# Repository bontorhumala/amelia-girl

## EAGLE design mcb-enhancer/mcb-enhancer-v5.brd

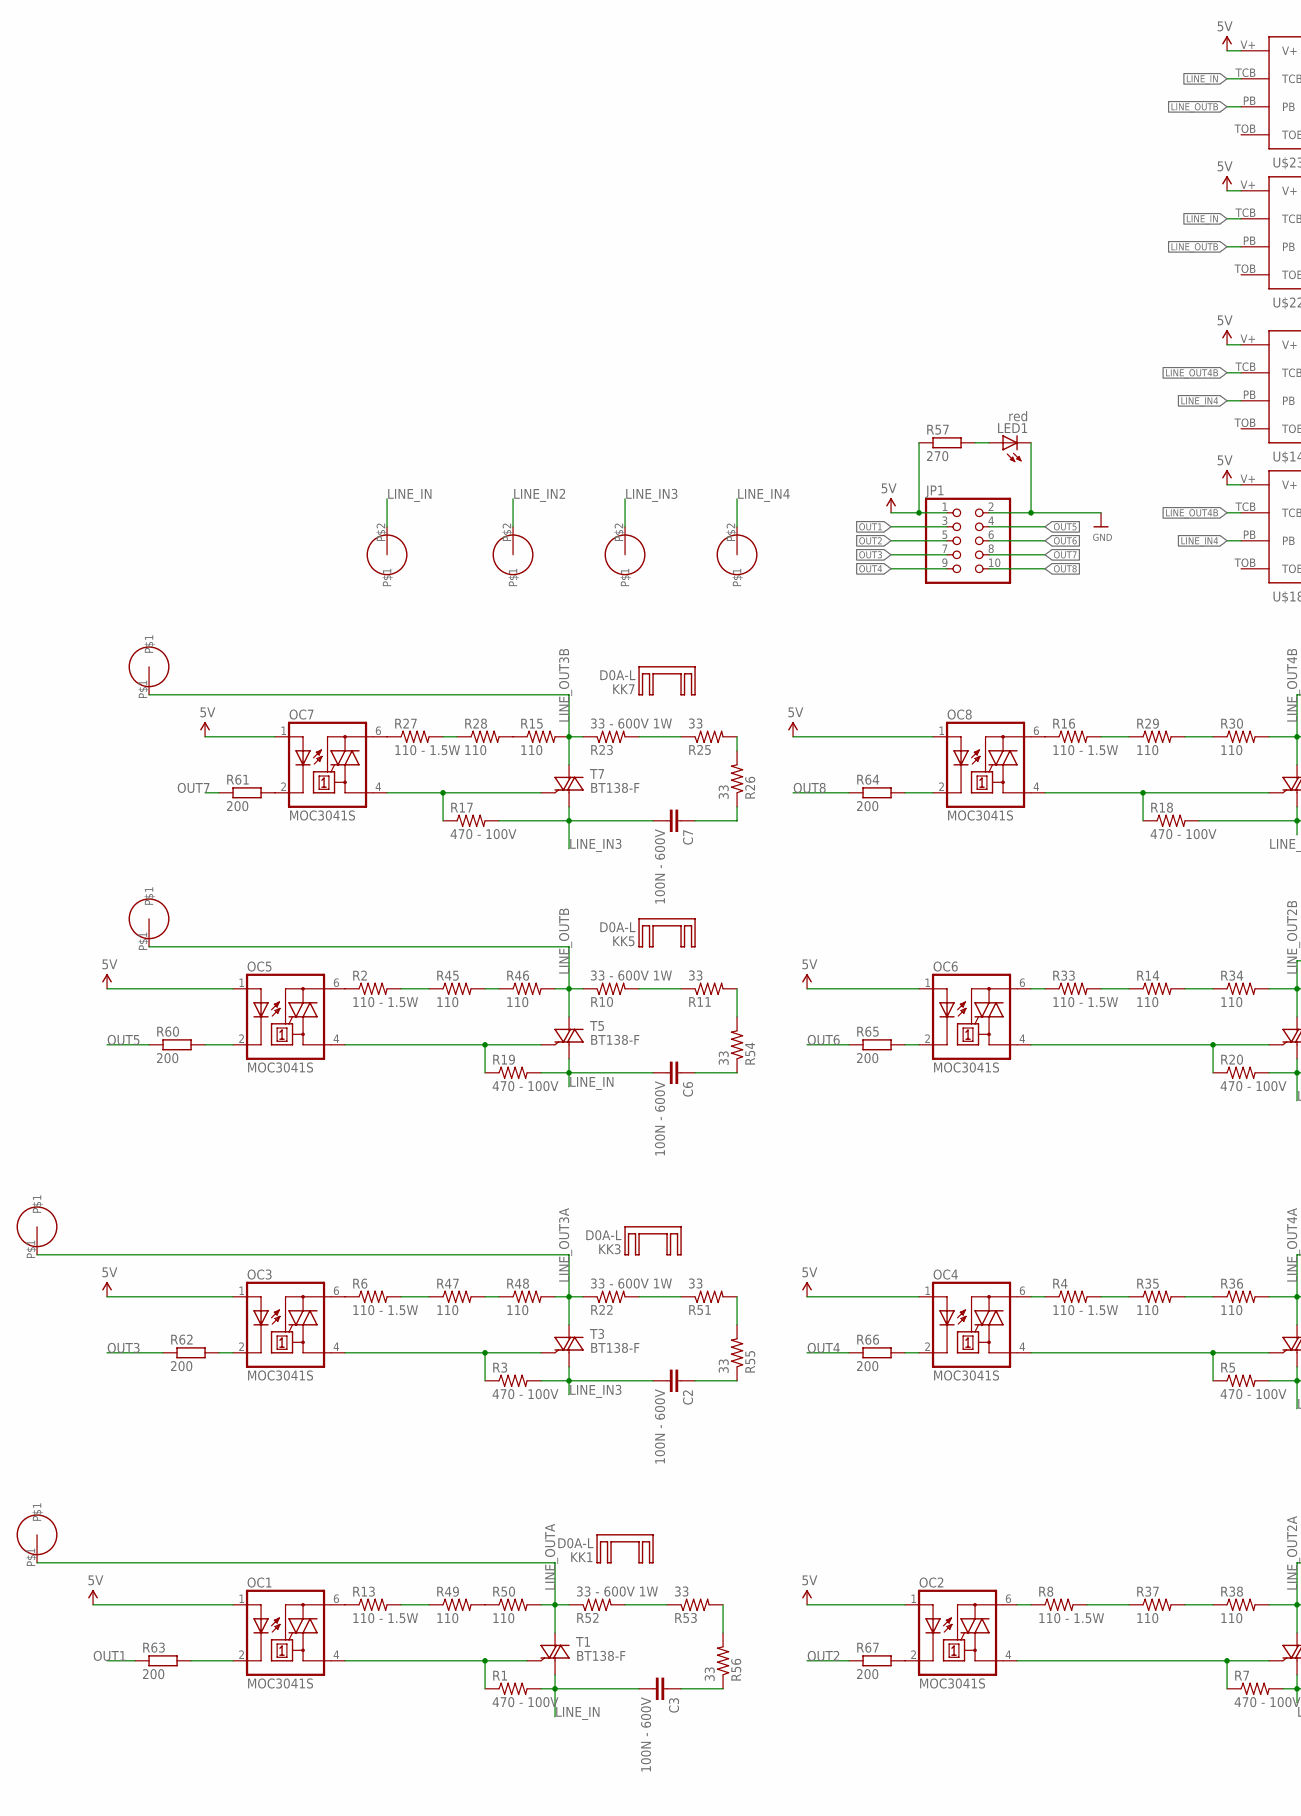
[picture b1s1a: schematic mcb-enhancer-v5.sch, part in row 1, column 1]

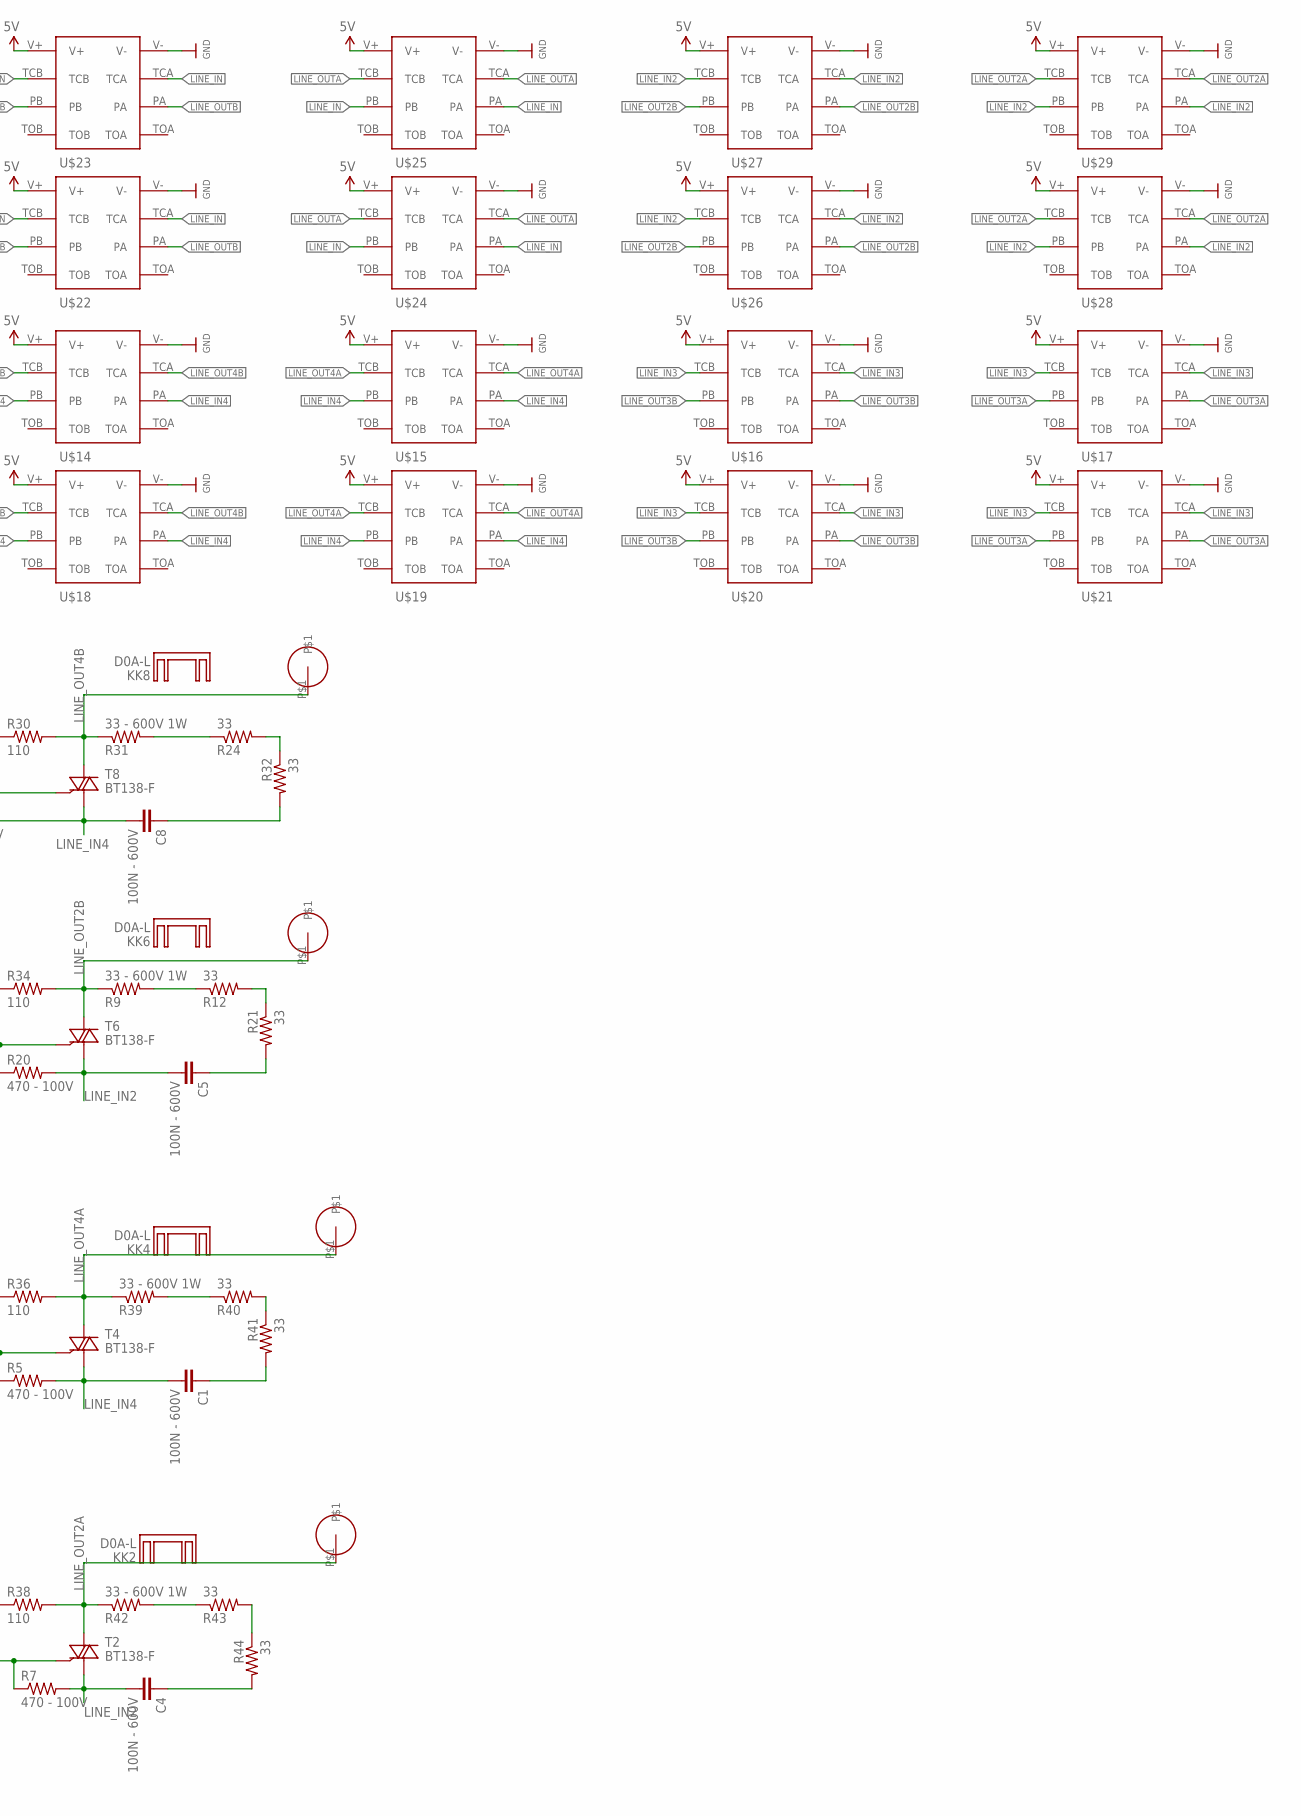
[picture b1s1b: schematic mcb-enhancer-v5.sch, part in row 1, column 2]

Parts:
C1, C2, C3, C4, C5, C6, C7, C8: 100N - 600V; C1210
JP1: PINHD-2X5; 2X05
KK1, KK2, KK3, KK4, KK5, KK6, KK7, KK8: D0A-L; D02A-L
LED1: red; CHIP-LED0805
OC1, OC2, OC3, OC4, OC5, OC6, OC7, OC8: MOC3041S; DIL6-SMD; MPN MOC3033S-M
R1, R3, R5, R7, R17, R18, R19, R20: 470 - 100V; R1206
R2, R4, R6, R8, R13, R16, R27, R33: 110 - 1.5W; R2512
R9, R10, R22, R23, R31, R39, R42, R52: 33 - 600V 1W; R1206
R11, R12, R21, R24, R25, R26, R32, R40, R41, R43, R44, R51, R53, R54, R55, R56: 33; R1206
R14, R15, R28, R29, R30, R34, R35, R36, R37, R38, R45, R46, R47, R48, R49, R50: 110; R2512
R57: 270; R0402
R60, R61, R62, R63, R64, R65, R66, R67: 200; R0603
T1, T2, T3, T4, T5, T6, T7, T8: BT138-F; TO220BF
U$1, U$2, U$3, U$4, U$5, U$6, U$7, U$8: CONN-SCREW-MINI
U$9, U$10, U$11, U$12: CONN; HC617
U$14, U$15, U$16, U$17, U$18, U$19, U$20, U$21, U$22, U$23, U$24, U$25, U$26, U$27, U$28, U$29: 9-1462038-9; TE-9-1462038-9

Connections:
5V: JP1.1, OC1.1 (A), OC2.1 (A), OC3.1 (A), OC4.1 (A), OC5.1 (A), OC6.1 (A), OC7.1 (A), OC8.1 (A), R57.1, U$14.V+, U$15.V+, U$16.V+, U$17.V+, U$18.V+, U$19.V+, U$20.V+, U$21.V+, U$22.V+, U$23.V+, U$24.V+, U$25.V+, U$26.V+, U$27.V+, U$28.V+, U$29.V+
GND: JP1.2, LED1.C, U$14.V-, U$15.V-, U$16.V-, U$17.V-, U$18.V-, U$19.V-, U$20.V-, U$21.V-, U$22.V-, U$23.V-, U$24.V-, U$25.V-, U$26.V-, U$27.V-, U$28.V-, U$29.V-
LINE_IN: C3.2, C6.2, R1.2, R19.2, T1.T1 (A1), T5.T1 (A1), U$9.P$2, U$22.TCA, U$22.TCB, U$23.TCA, U$23.TCB, U$24.PA, U$24.PB, U$25.PA, U$25.PB
LINE_IN2: C4.2, C5.2, R7.2, R20.2, T2.T1 (A1), T6.T1 (A1), U$10.P$2, U$26.TCA, U$26.TCB, U$27.TCA, U$27.TCB, U$28.PA, U$28.PB, U$29.PA, U$29.PB
LINE_IN3: C2.2, C7.2, R3.2, R17.2, T3.T1 (A1), T7.T1 (A1), U$11.P$2, U$16.TCA, U$16.TCB, U$17.TCA, U$17.TCB, U$20.TCA, U$20.TCB, U$21.TCA, U$21.TCB
LINE_IN4: C1.2, C8.2, R5.2, R18.2, T4.T1 (A1), T8.T1 (A1), U$12.P$2, U$14.PA, U$14.PB, U$15.PA, U$15.PB, U$18.PA, U$18.PB, U$19.PA, U$19.PB
LINE_OUT2A: R38.2, R42.1, T2.T2 (A2), U$2.P$1, U$28.TCA, U$28.TCB, U$29.TCA, U$29.TCB
LINE_OUT2B: R9.1, R34.2, T6.T2 (A2), U$6.P$1, U$26.PA, U$26.PB, U$27.PA, U$27.PB
LINE_OUT3A: R22.1, R48.2, T3.T2 (A2), U$3.P$1, U$17.PA, U$17.PB, U$21.PA, U$21.PB
LINE_OUT3B: R15.2, R23.1, T7.T2 (A2), U$7.P$1, U$16.PA, U$16.PB, U$20.PA, U$20.PB
LINE_OUT4A: R36.2, R39.1, T4.T2 (A2), U$4.P$1, U$15.TCA, U$15.TCB, U$19.TCA, U$19.TCB
LINE_OUT4B: R30.2, R31.1, T8.T2 (A2), U$8.P$1, U$14.TCA, U$14.TCB, U$18.TCA, U$18.TCB
LINE_OUTA: R50.2, R52.1, T1.T2 (A2), U$1.P$1, U$24.TCA, U$24.TCB, U$25.TCA, U$25.TCB
LINE_OUTB: R10.1, R46.2, T5.T2 (A2), U$5.P$1, U$22.PA, U$22.PB, U$23.PA, U$23.PB
unnamed: OC5.6 (A2), R2.1
unnamed: OC2.6 (A2), R8.1
unnamed: OC3.4 (A1), R3.1, T3.G
unnamed: OC3.6 (A2), R6.1
unnamed: OC4.4 (A1), R5.1, T4.G
unnamed: OC1.2 (C), R63.2
unnamed: R9.2, R12.1
unnamed: R49.2, R50.1
unnamed: R52.2, R53.1
unnamed: OC1.6 (A2), R13.1
unnamed: OC1.4 (A1), R1.1, T1.G
unnamed: R8.2, R37.1
unnamed: OC2.4 (A1), R7.1, T2.G
unnamed: R45.2, R46.1
unnamed: OC2.2 (C), R67.2
unnamed: R23.2, R25.1
unnamed: R25.2, R26.2
unnamed: OC3.2 (C), R62.2
unnamed: OC4.2 (C), R66.2
unnamed: C7.1, R26.1
unnamed: R12.2, R21.1
unnamed: OC7.2 (C), R61.2
unnamed: OC7.6 (A2), R27.1
unnamed: OC8.2 (C), R64.2
unnamed: R15.1, R28.2
unnamed: R27.2, R28.1
unnamed: OC5.2 (C), R60.2
unnamed: OC6.2 (C), R65.2
unnamed: R16.2, R29.1
unnamed: OC7.4 (A1), R17.1, T7.G
unnamed: OC8.6 (A2), R16.1
unnamed: OC8.4 (A1), R18.1, T8.G
unnamed: R29.2, R30.1
unnamed: R37.2, R38.1
unnamed: OC5.4 (A1), R19.1, T5.G
unnamed: OC6.4 (A1), R20.1, T6.G
unnamed: C5.1, R21.2
unnamed: OC4.6 (A2), R4.1
unnamed: C8.1, R32.2
unnamed: R24.2, R32.1
unnamed: R24.1, R31.2
unnamed: R4.2, R35.1
unnamed: R35.2, R36.1
unnamed: OC6.6 (A2), R33.1
unnamed: R14.1, R33.2
unnamed: R14.2, R34.1
unnamed: R39.2, R40.1
unnamed: C1.1, R41.2
unnamed: R40.2, R41.1
unnamed: C4.1, R44.2
unnamed: R43.2, R44.1
unnamed: R42.2, R43.1
unnamed: R47.2, R48.1
unnamed: R13.2, R49.1
unnamed: R6.2, R47.1
unnamed: R2.2, R45.1
unnamed: R22.2, R51.1
unnamed: R10.2, R11.1
unnamed: C3.1, R56.1
unnamed: R53.2, R56.2
unnamed: C2.1, R55.1
unnamed: R51.2, R55.2
unnamed: C6.1, R54.1
unnamed: R11.2, R54.2
unnamed: LED1.A, R57.2
OUT1: JP1.3, R63.1
OUT2: JP1.5, R67.1
OUT3: JP1.7, R62.1
OUT4: JP1.9, R66.1
OUT5: JP1.4, R60.1
OUT6: JP1.6, R65.1
OUT7: JP1.8, R61.1
OUT8: JP1.10, R64.1

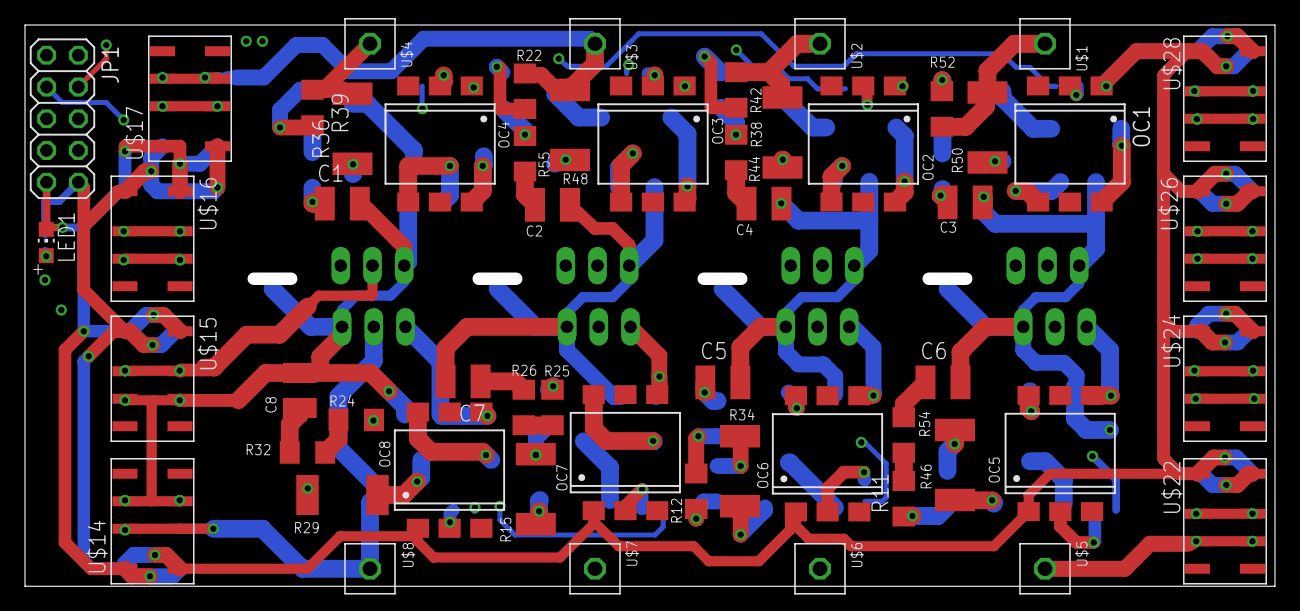
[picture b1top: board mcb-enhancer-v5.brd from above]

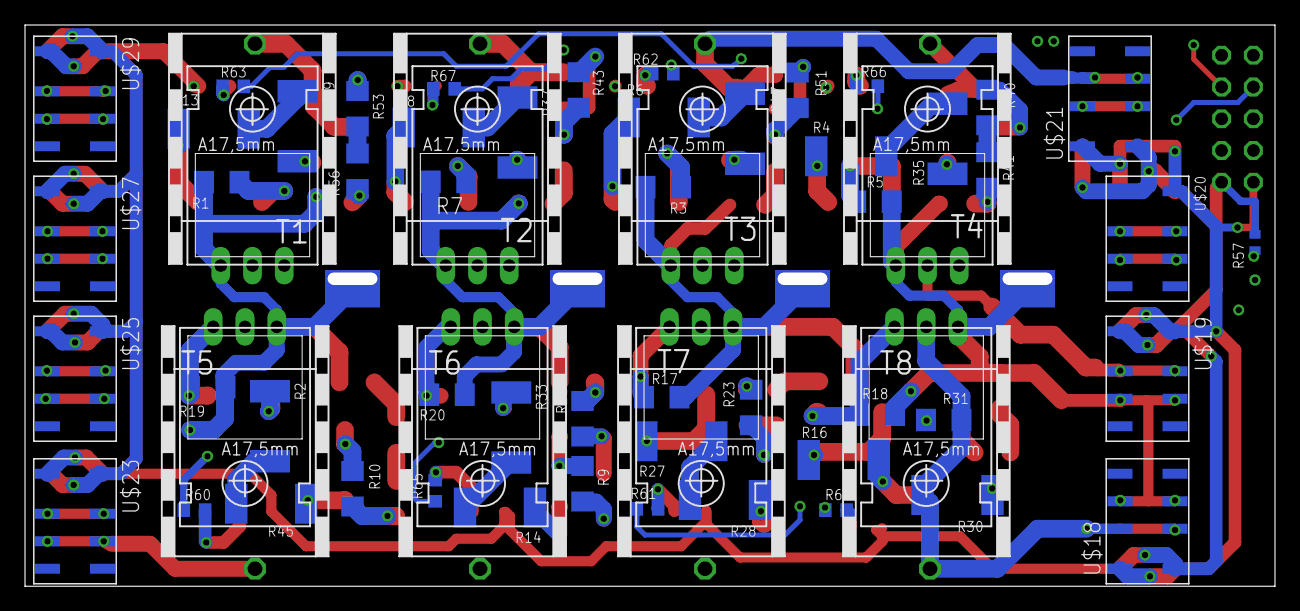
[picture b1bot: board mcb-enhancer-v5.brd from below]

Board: 4 copper layers, 100.0 x 44.9 mm, 127 parts (72 on the bottom side), 87 nets.

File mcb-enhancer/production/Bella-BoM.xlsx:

Ref | Part number | Description | Value |  | Amount | Link
LED1 | LED 0805 merah | Red LED SMD 0805 | - |  | 1 | Digikey |  | ok
JP1 | IDC2.54-2*5PL | Right angle pin header 5x2 | - |  | 1 | Aliexpress |  | ok
R57, R60, R61, R62, R63, R64, R65, R66, R67 | R0402 | Resistor SMD 0402, 16V | 330 Ohm |  | 9 | Digikey |  | ok
C1, C2, C3, C4, C5, C6, C7, C8 | C3225X7T2J104K160AC | Capacitor SMD 1210, minimum 600V - TDK Corp | 100 nF |  | 8 | Digikey |  | ok
R14, R15, R28, R29, R30, R34, R35, R36, R37, R38, R45, R46, R47, R48, R49, R50,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 | 1879524-2 | Resistor SMD 2512, 2Watt - TE Connectivity | 110 Ohm |  | 24 | Digikey |  | ok
R11, R12, R21, R24, R25, R26, R32, R40, R41, R43, R44, R51, R53, R54, R55, R56,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 | - | Resistor SMD 1206, 1Watt 600V | 33 Ohm |  | 24 | Digikey |  | ok
R1, R3, R5, R7, R17, R18, R19, R20 | - | Resistor SMD 1206, minimum 100V | 470 Ohm |  | 8 | Digikey |  | ok
U$14, U$15, U$16, U$17, U$18, U$19, U$20, U$21, U$22, U$23, U$24, U$25, U$26, U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 | 9-1462038-9 | TE Relay DPDT 250VAC, 5A contact rating, 5VDC coil | - |  | 16 | Alibaba | Digikey | ok
T1, T2, T3, T4, T5, T6, T7, T8 | BT139-600 | BT139 Triac | - |  | 8 | Aliexpress |  | ok
U$9, U$10, U$11, U$12 | HC617 | Hegxing Male PCB terminal HC617 | - |  | 4 | Manufacturer
U$1, U$2, U$3, U$4, U$5, U$6, U$7, U$8 | 8737 | Mini female binding post connector Keystone Electronic | - |  | 8 | Digikey |  | ok
KK1, KK2, KK3, KK4, KK5, KK6, KK7, KK8 | EH22x15x10BN | Heatsink D02A-L | - |  | 8 | Aliexpress |  | ok
OC1, OC2, OC3, OC4, OC5, OC6, OC7, OC8 | MOC3041 SMD | Optocoupler zero crossing SMD type | - |  | 8 | Aliexpress |  | ok

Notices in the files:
parts and their libraries:
SparkFun-Passives: Licensing: CC v3.0 Share-Alike You are welcome to use this library for commercial purposes.
microbuilder: This work is placed in the public domain, and may be freely used for commercial and non-commercial work with the following conditions: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
